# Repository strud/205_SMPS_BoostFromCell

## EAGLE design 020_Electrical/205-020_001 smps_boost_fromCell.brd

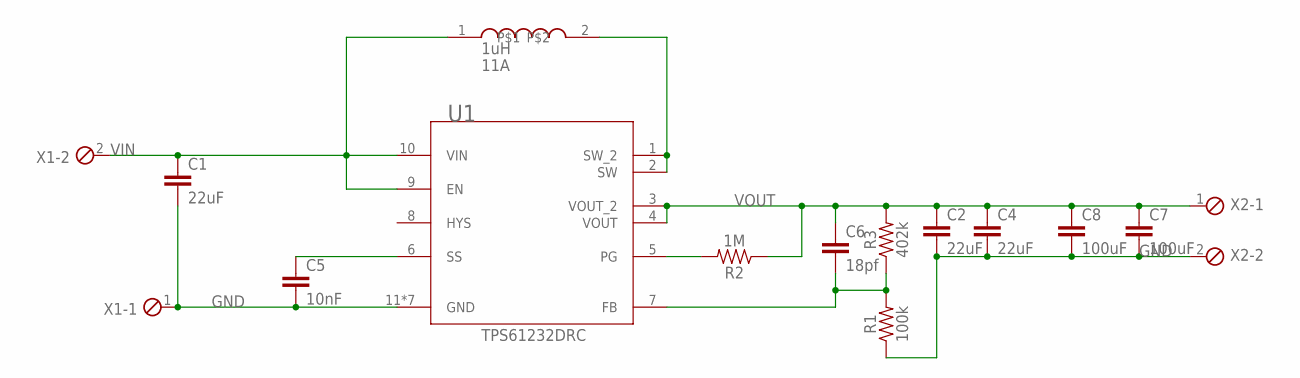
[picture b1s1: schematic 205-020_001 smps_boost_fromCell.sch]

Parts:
C1, C2, C4: 22uF; 0805
C5: 10nF; 0603
C6: 18pf; 0805
C7, C8: 100uF; 1206
R1: 100k; 0603
R2: 1M; 0603
R3: 402k; 0603
U1: TPS61232DRCR; DRC0010G
U$1: 1uH; 07A7
X1, X2: MPT2; 2POL254

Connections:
GND: C1.2, C2.2, C4.2, C5.2, C7.2, C8.2, R1.1, U1.11 (GND), U1.11A (GND), U1.11B (GND), U1.11C (GND), U1.11D (GND), U1.11E (GND), U1.11F (GND), X1.1, X2.2
unnamed: U1.1 (SW_2), U1.2 (SW), U$1.2
unnamed: C5.1, U1.6 (SS)
unnamed: R2.2, U1.5 (PG)
unnamed: C6.2, R1.2, R3.1, U1.7 (FB)
VIN: C1.1, U1.9 (EN), U1.10 (VIN), U$1.1, X1.2
VOUT: C2.1, C4.1, C6.1, C7.1, C8.1, R2.1, R3.2, U1.3 (VOUT_2), U1.4 (VOUT), X2.1

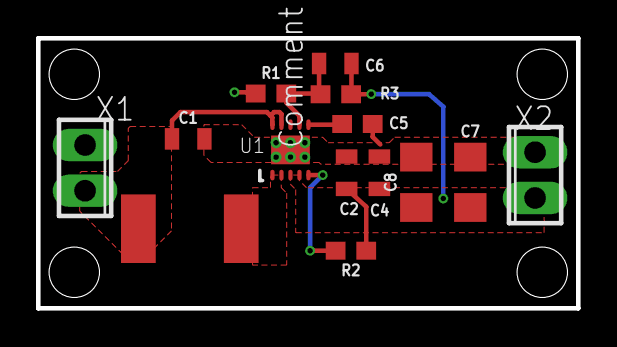
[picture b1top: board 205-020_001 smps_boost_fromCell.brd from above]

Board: 2 copper layers, 30.0 x 15.0 mm, 14 parts (0 on the bottom side), 7 nets.

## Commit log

2020-11-06 finalised for manufacture
2022-12-16 incremental

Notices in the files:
parts and their libraries:
SparkFun-Capacitors: Licensing: Creative Commons ShareAlike 4.0 International - https://creativecommons.org/licenses/by-sa/4.0
